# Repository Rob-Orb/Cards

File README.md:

# Cards

## KiCad Configuration

In Eeschema :
You should find the library in the folder [kicad-symbols](kicad-symbols). Link this library to kicad.

- Preferences -> Symbol Library Manager -> Browse Library...

| Nickname | Library Path | Plugin Type |
| ------------- | ------------- | ------------- |
| Rob | ../../Rob-5.lib | Legacy |

In PCBNew :
- Preferences -> Footprint Library Manager -> Append Library

| Nickname | Library Path | Plugin Type |
| ------------- | ------------- | ------------- |
| Rob | https://github.com/Rob-Orb/Rob-5.0.pretty | Github |

Or if you want to modify the library after cloning it :

| Nickname | Library Path | Plugin Type |
| ------------- | ------------- | ------------- |
| Rob | ${KIPRJMOD}/../../../Rob-5.0.pretty | KiCad |

And clone the library [Rob.pretty](https://github.com/Rob-Orb/Rob.pretty) at the corresponding path (next to this repo).

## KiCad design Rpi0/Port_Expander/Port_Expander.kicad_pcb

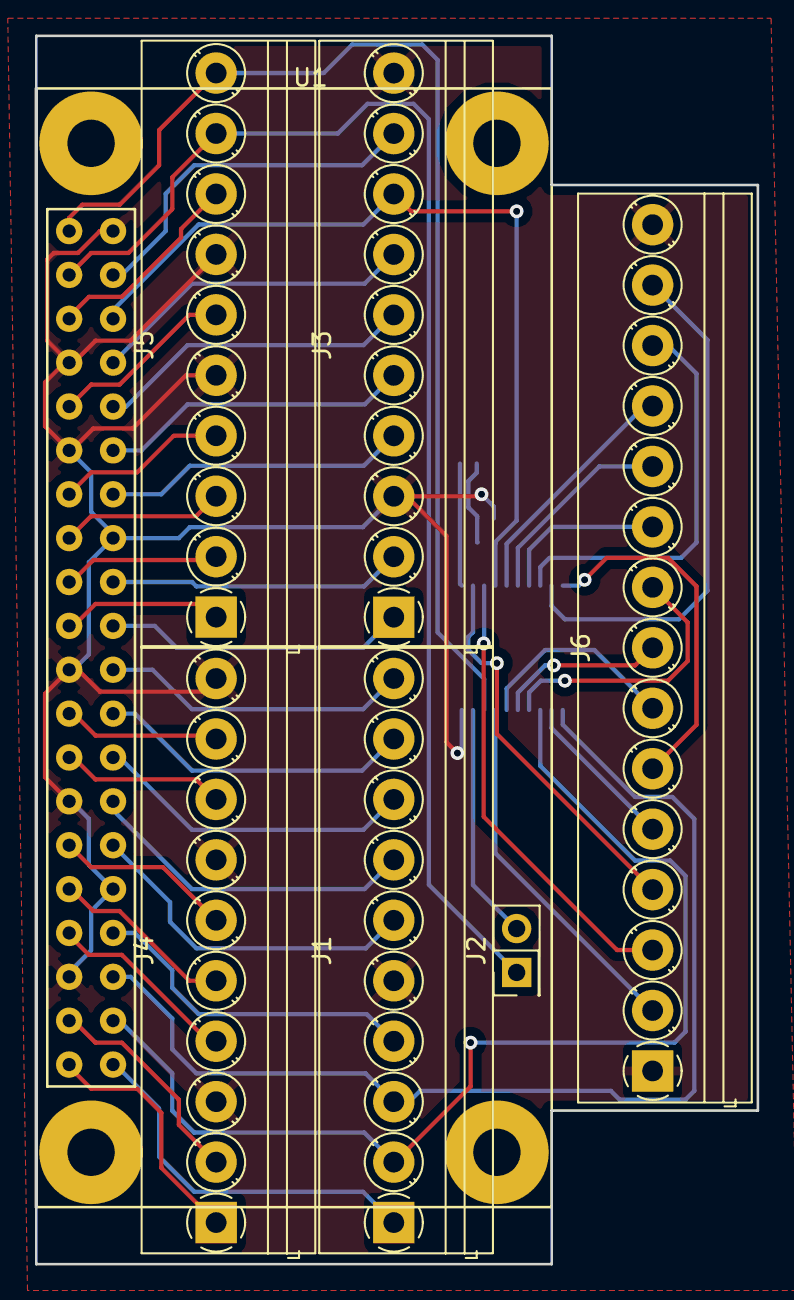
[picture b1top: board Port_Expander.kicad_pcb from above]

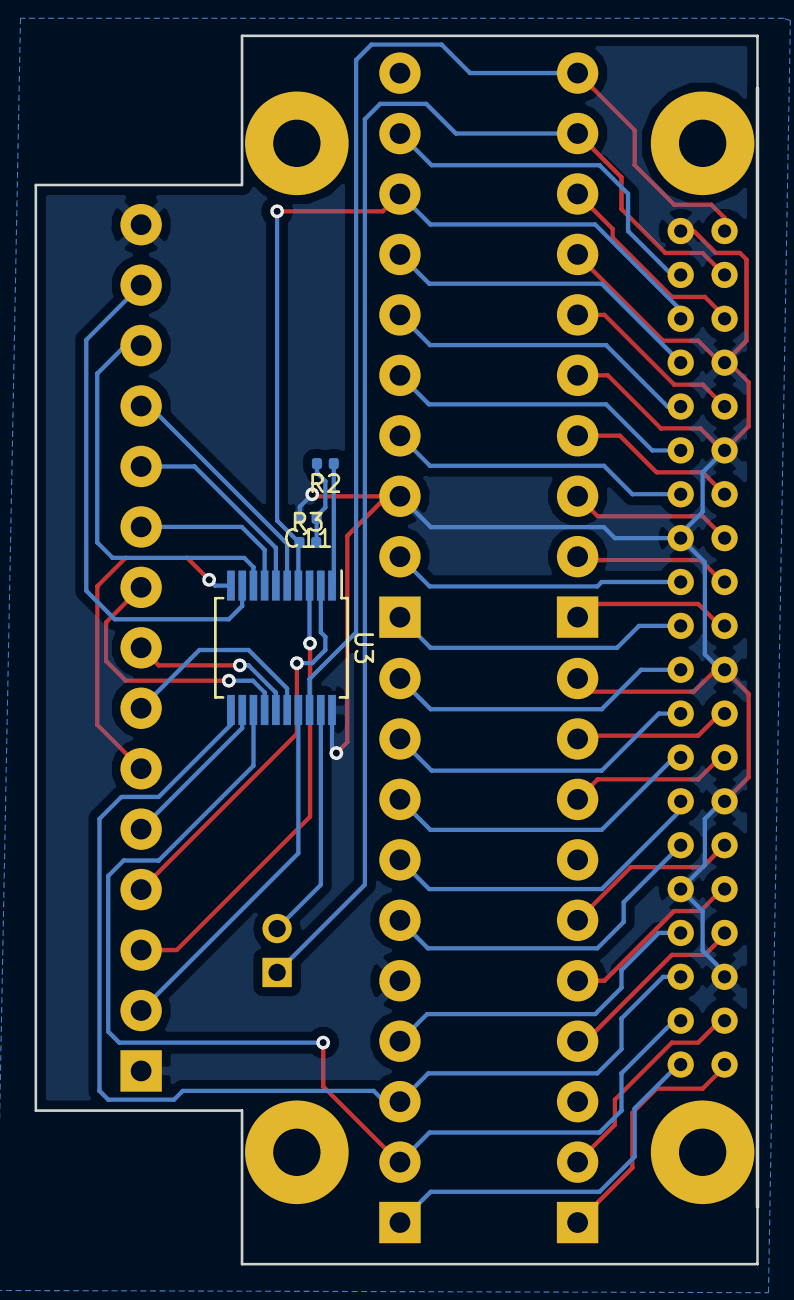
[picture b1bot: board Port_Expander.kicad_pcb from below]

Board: 2 copper layers, 41.8 x 71.1 mm, 11 parts (4 on the bottom side), 49 nets.

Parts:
C11: 1uF; C_0402_1005Metric
J1, J3, J4, J5: Screw_Terminal_01x10; TerminalBlock_Phoenix_MKDS-1,5-10-3.5-H_1x10_P3.50mm_Horizo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
J2: Conn_02x01; PinHeader_2x01_P2.54mm_Vertical
J6: Screw_Terminal_01x15; TerminalBlock_Phoenix_MKDS-1,5-15-3.5-H_1x15_P3.50mm_Horizo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
R2: 10k; R_0402_1005Metric
R3: 470; R_0402_1005Metric
U1: RPI0-Template; RPi0_Template
U3: PIC16F1509-ISS; SSOP-20_5.3x7.2mm_P0.65mm

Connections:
+3V3: R2.1, U3.1
/PIC16LF1509/RA2: J6.2, U3.17
/PIC16LF1509/RA4: J6.3, U3.3
/PIC16LF1509/RA5: J6.4, U3.2
/PIC16LF1509/RB5: J6.5, U3.12
/PIC16LF1509/RB7: J6.6, U3.10
/PIC16LF1509/RC0: J6.7, U3.16
/PIC16LF1509/RC1: J6.8, U3.15
/PIC16LF1509/RC2: J6.9, U3.14
/PIC16LF1509/RC3: J6.10, U3.7
/PIC16LF1509/RC4: J6.11, U3.6
/PIC16LF1509/RC5: J6.12, U3.5
/PIC16LF1509/RC6: J6.13, U3.8
/PIC16LF1509/RC7: J6.14, U3.9
GND: C11.2, J1.5, J3.3, J3.10, J4.3, J4.7, J4.10, J5.5, J5.7, J6.1, J6.15, U1.6, U1.9, U1.14, U1.20, U1.25, U1.30, U1.34, U1.39, U3.20
ISCP_CLK: J5.10, U1.40, U3.18
ISCP_DAT: J2.1, J5.9, U1.38
MCLR: J3.8, R3.1, U1.35, U3.4
unnamed: C11.1, R2.2, R3.2
unnamed: J1.1, U1.1
unnamed: J1.4, U1.7
unnamed: J1.6, U1.11
unnamed: J1.7, U1.13
unnamed: J1.8, U1.15
unnamed: J1.9, U1.17
unnamed: J1.10, U1.19
unnamed: J2.2, U3.19
unnamed: J3.1, U1.21
unnamed: J3.2, U1.23
unnamed: J3.4, U1.27
unnamed: J3.5, U1.29
unnamed: J3.6, U1.31
unnamed: J3.7, U1.33
unnamed: J3.9, U1.37
unnamed: J4.1, U1.2
unnamed: J4.2, U1.4
unnamed: J4.4, U1.8
unnamed: J4.5, U1.10
unnamed: J4.6, U1.12
unnamed: J4.8, U1.16
unnamed: J4.9, U1.18
unnamed: J5.1, U1.22
unnamed: J5.2, U1.24
unnamed: J5.3, U1.26
unnamed: J5.4, U1.28
unnamed: J5.6, U1.32
unnamed: J5.8, U1.36
SCL: J1.3, U1.5, U3.11
SDA: J1.2, U1.3, U3.13

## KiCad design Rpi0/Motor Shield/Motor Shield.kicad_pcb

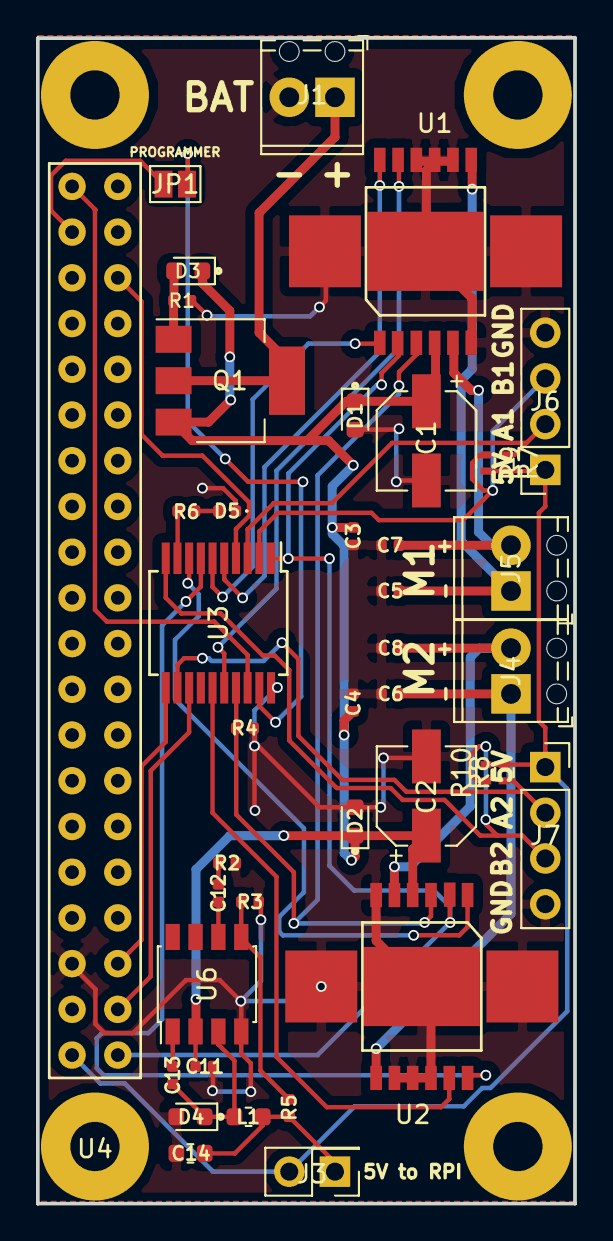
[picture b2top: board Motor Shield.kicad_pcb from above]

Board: 2 copper layers, 29.8 x 64.8 mm, 41 parts (0 on the bottom side), 35 nets.

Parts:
C1, C2: 100uF; CP_Elec_5x5.3
C3, C4: 100nF; C_0402_1005Metric
C5, C6, C7, C8, C13: 10nF; C_0402_1005Metric
C11: 10uF; C_0402_1005Metric
C12: 2.2nF; C_0402_1005Metric
C14: 22uF; C_0603_1608Metric
D1, D2: < 40V; D_0603_1608Metric
D3: 10V; D_0603_1608Metric
D4: 40V; D_0603_1608Metric
D5: GREEN; LED_0402_1005Metric
J1, J4, J5: Screw_Terminal_01x02; TerminalBlock_Phoenix_MPT-0,5-2-2.54_1x02_P2.54mm_Horizontal
J3: Conn_02x01; PinHeader_2x01_P2.54mm_Vertical
J6, J7: Conn_01x04_Female; PinSocket_1x04_P2.54mm_Vertical
JP1: SolderJumper_2_Open; SolderJumper-2_P1.3mm_Open_Pad1.0x1.5mm
L1: 15uH; L_0603_1608Metric
Q1: Q_PMOS_GDSD; SOT-223
R1, R3, R4: 10k; R_0402_1005Metric
R2: 15k; R_0402_1005Metric
R5: 28.7k; R_0402_1005Metric
R6: 50; R_0402_1005Metric
R7, R8, R9, R10: 1k; R_0402
U1, U2: IFX9201SG
U3: PIC16F1509-ISS; SSOP-20_5.3x7.2mm_P0.65mm
U4: RPI0-Template; RPi0_Template
U6: ACT4060A; SSOP-8_3.95x5.21x3.27mm_P1.27mm

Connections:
5V: C14.1, J3.1, L1.2, R5.1
+3V3: U1.2, U2.2, U3.1, U4.1
+5V: J3.2, J6.1, J7.1, R7.2, R8.2, R9.2, R10.2, U4.2
/PIC16LF1509/Bonus: R6.1, U3.9
A1: J6.2, R7.1, U3.3
A2: J7.2, R8.1, U3.12
B1: J6.3, R9.1, U3.2
B2: J7.3, R10.1, U3.10
BAT+: J1.1, Q1.2, Q1.4
BAT-: C1.2, C2.2, C3.2, C4.2, C5.2, C6.2, C7.2, C8.2, C11.2, C14.2, D1.2, D2.2, D4.2, D5.1, J1.2, J6.4, J7.4, R1.2, R2.2, R3.2, R4.2, U1.6, U1.8, U1.9, U1.10, U1.~, U2.6, U2.8, U2.9, U2.10, U2.~, U3.20, U4.6, U6.4
BAT-PROT+: C1.1, C2.1, C3.1, C4.1, C11.1, D1.1, D2.1, D3.1, Q1.3, U1.4, U2.4, U6.2
DIR1: U1.1, U3.6
DIR2: U2.1, U3.8
EN1: U1.11, U3.16
EN2: U2.11, U3.15
ERROR: R4.1, U1.3, U2.3, U3.17
ICSP_CLK: U3.18, U4.40
ICSP_DAT: JP1.1, U4.38
MCLR: U3.4, U4.35
unnamed: C12.1, U6.6
unnamed: C12.2, R2.1
unnamed: C13.1, U6.1
unnamed: C13.2, D4.1, L1.1, U6.3
unnamed: D3.2, Q1.1, R1.1
unnamed: D5.2, R6.2
unnamed: JP1.2, U3.19
unnamed: R3.1, R5.2, U6.5
OUT1: C7.1, J5.2, U1.5
OUT2: C5.1, J5.1, U1.7
OUT3: C8.1, J4.2, U2.5
OUT4: C6.1, J4.1, U2.7
PWM1: U1.12, U3.5
PWM2: U2.12, U3.7
SCL: U3.11, U4.5
SDA: U3.13, U4.3

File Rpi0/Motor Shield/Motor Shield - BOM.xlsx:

Reference | Value | Footprint | Datasheet
R3 | 470 | Resistor_SMD:R_0402_1005Metric
D1 | < 40V | Diode_SMD:D_0603_1608Metric
D2 | < 40V | Diode_SMD:D_0603_1608Metric
C3 | 100nF | Capacitor_SMD:C_0402_1005Metric
C4 | 100nF | Capacitor_SMD:C_0402_1005Metric
C9 | 100nF | Capacitor_SMD:C_0402_1005Metric
C1 | 100uF | Capacitor_SMD:CP_Elec_5x5.3
C2 | 100uF | Capacitor_SMD:CP_Elec_5x5.3
R1 | 10k | Resistor_SMD:R_0402_1005Metric
R2 | 10k | Resistor_SMD:R_0402_1005Metric
C5 | 10nF | Capacitor_SMD:C_0603_1608Metric
C7 | 10nF | Capacitor_SMD:C_0603_1608Metric
C6 | 10nF | Capacitor_SMD:C_0603_1608Metric
C8 | 10nF | Capacitor_SMD:C_0603_1608Metric
C10 | 10uF | Capacitor_SMD:C_0603_1608Metric
D3 | 10V | Diode_SMD:D_0603_1608Metric
C11 | 1uF | Capacitor_SMD:C_0402_1005Metric
J6 | Conn_01x04_Female | Connector_PinSocket_2.54mm:PinSocket_1x04_P2.54mm_Vertical | ~
J7 | Conn_01x04_Female | Connector_PinSocket_2.54mm:PinSocket_1x04_P2.54mm_Vertical | ~
J3 | Conn_02x01 | Connector_PinHeader_2.54mm:PinHeader_2x01_P2.54mm_Vertical | ~
J2 | Conn_02x01 | Connector_PinHeader_2.54mm:PinHeader_2x01_P2.54mm_Vertical | ~
U1 | IFX9201SG | Rob-5.0:IFX9201SG
U2 | IFX9201SG | Rob-5.0:IFX9201SG
U5 | LD1117S50TR_SOT223 | Package_TO_SOT_SMD:SOT-223-3_TabPin2 | http://www.st.com/st-web-ui/static/active/en/resource/techni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
U3 | PIC16F1509-ISS | Package_SO:SSOP-20_5.3x7.2mm_P0.65mm | http://ww1.microchip.com/downloads/en/DeviceDoc/41609A.pdf
Q1 | Q_PMOS_GDSD | Package_TO_SOT_SMD:SOT-223
U4 | RPI0-Template | Rob-5.0:RPi0_Template
J1 | Screw_Terminal_01x02 | TerminalBlock_Phoenix:TerminalBlock_Phoenix_MPT-0,5-2-2.54_1x02_P2.54mm_Horizon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 | ~
J5 | Screw_Terminal_01x02 | TerminalBlock_Phoenix:TerminalBlock_Phoenix_MPT-0,5-2-2.54_1x02_P2.54mm_Horizon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 | ~
J4 | Screw_Terminal_01x02 | TerminalBlock_Phoenix:TerminalBlock_Phoenix_MPT-0,5-2-2.54_1x02_P2.54mm_Horizon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 | ~

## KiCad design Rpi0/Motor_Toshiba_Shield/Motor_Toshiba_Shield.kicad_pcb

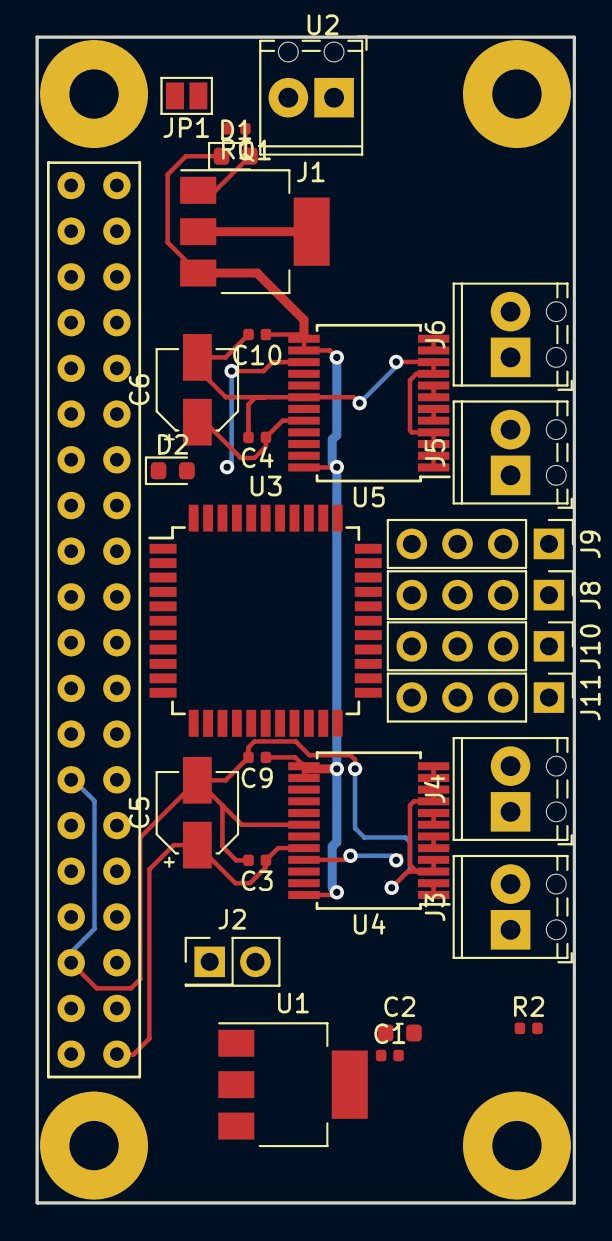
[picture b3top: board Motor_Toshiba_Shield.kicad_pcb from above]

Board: 2 copper layers, 29.8 x 64.8 mm, 29 parts (0 on the bottom side), 45 nets.

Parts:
C1, C3, C4, C9, C10: 100nF; C_0402_1005Metric
C2: 10uF; C_0603_1608Metric
C5, C6: 10uF; CP_Elec_4x5.4
D1: D_Schottky; D_0603_1608Metric
D2: LED; LED_0603_1608Metric
J1, J3, J4, J5, J6: Screw_Terminal_01x02; TerminalBlock_Phoenix_MPT-0,5-2-2.54_1x02_P2.54mm_Horizontal
J2: Conn_02x01; PinHeader_2x01_P2.54mm_Vertical
J8, J9, J10, J11: Conn_01x04_Female; PinHeader_1x04_P2.54mm_Vertical
JP1: SolderJumper_2_Open; SolderJumper-2_P1.3mm_Open_Pad1.0x1.5mm
Q1: Q_NMOS_GDSD; SOT-223
R1: 10k; R_0402_1005Metric
R2: 50; R_0402_1005Metric
U1: LD1117S50TR_SOT223; SOT-223-3_TabPin2
U2: RPI0-Template; RPi0_Template
U3: PIC16F1777-TQFP; TQFP-44_10x10mm_P0.8mm
U4, U5: TB6612FNG; SSOP-24_5.3x8.2mm_P0.65mm

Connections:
+3V3: C3.1, C4.1, C5.1, C6.1, U2.1, U3.7, U3.28, U4.20, U5.20
+5V: C2.1, J2.1, J8.1, J9.1, J10.1, J11.1, U1.2
A1: J8.2, U3.23
A2: J9.2, U3.31
A3: J10.2, U3.8
A4: J11.2, U3.10
B1: J8.3, U3.24
B2: J9.3, U3.30
B3: J10.3, U3.9
B4: J11.3, U3.11
BAT+: J1.1, Q1.2, Q1.4
BAT-: C1.2, C2.2, C3.2, C4.2, C5.2, C6.2, C9.2, C10.2, D2.1, J1.2, J8.4, J9.4, J10.4, J11.4, R1.2, U1.1, U2.6, U2.14, U2.39, U3.6, U3.29, U4.3, U4.4, U4.9, U4.10, U4.18, U5.3, U5.4, U5.9, U5.10, U5.18
BAT-PROT+: C1.1, C9.1, C10.1, D1.1, Q1.3, U1.3, U4.13, U4.14, U4.24, U5.13, U5.14, U5.24
EN1: U3.25, U5.19
EN2: U3.26, U4.19
ICSP_CLK: U2.40, U3.16
ICSP_DAT: JP1.2, U2.38
INA1: U3.38, U5.21
INA2: U3.39, U5.22
INA3: U3.2, U4.21
INA4: U3.3, U4.22
INB1: U3.40, U5.17
INB2: U3.41, U5.16
INB3: U3.4, U4.17
INB4: U3.5, U4.16
MCLR: U2.35, U3.18
unnamed: D1.2, Q1.1, R1.1
unnamed: D2.2, R2.2
unnamed: J2.2, U2.2
unnamed: J3.1, U4.1, U4.2
unnamed: J3.2, U4.5, U4.6
unnamed: J4.1, U4.7, U4.8
unnamed: J4.2, U4.11, U4.12
unnamed: J5.1, U5.1, U5.2
unnamed: J5.2, U5.5, U5.6
unnamed: J6.1, U5.7, U5.8
unnamed: J6.2, U5.11, U5.12
unnamed: JP1.1, U3.17
unnamed: R2.1, U3.14
PWM1: U3.20, U5.23
PWM2: U3.21, U5.15
PWM3: U3.22, U4.23
PWM4: U3.19, U4.15
SCL: U2.5, U3.37
SDA: U2.3, U3.42

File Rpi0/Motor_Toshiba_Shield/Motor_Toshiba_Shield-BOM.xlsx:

Reference | Value | Footprint | Datasheet
R3 | 470 | Resistor_SMD:R_0402_1005Metric
C3 | 100nF | Capacitor_SMD:C_0402_1005Metric | ~
C4 | 100nF | Capacitor_SMD:C_0402_1005Metric | ~
C10 | 100nF | Capacitor_SMD:C_0402_1005Metric | ~
C9 | 100nF | Capacitor_SMD:C_0402_1005Metric | ~
C1 | 100nF | Capacitor_SMD:C_0402_1005Metric | ~
R1 | 10k | Resistor_SMD:R_0402_1005Metric | ~
R2 | 10k | Resistor_SMD:R_0402_1005Metric
C5 | 10uF | Capacitor_SMD:CP_Elec_4x5.4 | ~
C6 | 10uF | Capacitor_SMD:CP_Elec_4x5.4 | ~
C2 | 10uF | Capacitor_SMD:C_0603_1608Metric | ~
C11 | 1uF | Capacitor_SMD:C_0402_1005Metric
J8 | Conn_01x04_Female | Connector_PinHeader_2.54mm:PinHeader_1x04_P2.54mm_Vertical | ~
J9 | Conn_01x04_Female | Connector_PinHeader_2.54mm:PinHeader_1x04_P2.54mm_Vertical | ~
J10 | Conn_01x04_Female | Connector_PinHeader_2.54mm:PinHeader_1x04_P2.54mm_Vertical | ~
J11 | Conn_01x04_Female | Connector_PinHeader_2.54mm:PinHeader_1x04_P2.54mm_Vertical | ~
J2 | Conn_02x01 | Connector_PinHeader_2.54mm:PinHeader_2x01_P2.54mm_Vertical | ~
J7 | Conn_02x01 | Connector_PinHeader_2.54mm:PinHeader_2x01_P2.54mm_Vertical | ~
D1 | D_Schottky | Diode_SMD:D_0603_1608Metric | ~
U1 | LD1117S50TR_SOT223 | Package_TO_SOT_SMD:SOT-223-3_TabPin2 | http://www.st.com/st-web-ui/static/active/en/resource/techni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
U3 | MCP23008_SSOP | Package_SO:SSOP-20_5.3x7.2mm_P0.65mm | http://ww1.microchip.com/downloads/en/DeviceDoc/21919e.pdf
U6 | PIC16F1509-ISS | Package_SO:SSOP-20_5.3x7.2mm_P0.65mm | http://ww1.microchip.com/downloads/en/DeviceDoc/41609A.pdf
Q1 | Q_NMOS_GDSD | Package_TO_SOT_SMD:SOT-223 | ~
U2 | RPI0-Template | Rob-5.0:RPi0_Template
J1 | Screw_Terminal_01x02 | TerminalBlock_Phoenix:TerminalBlock_Phoenix_MPT-0,5-2-2.54_1x02_P2.54mm_Horizon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 | ~
J5 | Screw_Terminal_01x02 | TerminalBlock_Phoenix:TerminalBlock_Phoenix_MPT-0,5-2-2.54_1x02_P2.54mm_Horizon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 | ~
J6 | Screw_Terminal_01x02 | TerminalBlock_Phoenix:TerminalBlock_Phoenix_MPT-0,5-2-2.54_1x02_P2.54mm_Horizon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 | ~
J3 | Screw_Terminal_01x02 | TerminalBlock_Phoenix:TerminalBlock_Phoenix_MPT-0,5-2-2.54_1x02_P2.54mm_Horizon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 | ~
J4 | Screw_Terminal_01x02 | TerminalBlock_Phoenix:TerminalBlock_Phoenix_MPT-0,5-2-2.54_1x02_P2.54mm_Horizon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 | ~
JP1 | SolderJumper_2_Open | Jumper:SolderJumper-2_P1.3mm_Open_Pad1.0x1.5mm | ~
JP2 | SolderJumper_2_Open | Jumper:SolderJumper-2_P1.3mm_Open_Pad1.0x1.5mm | ~
JP3 | SolderJumper_2_Open | Jumper:SolderJumper-2_P1.3mm_Open_Pad1.0x1.5mm | ~
U5 | TB6612FNG | Package_SO:SSOP-24_5.3x8.2mm_P0.65mm | https://toshiba.semicon-storage.com/us/product/linear/motord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
U4 | TB6612FNG | Package_SO:SSOP-24_5.3x8.2mm_P0.65mm | https://toshiba.semicon-storage.com/us/product/linear/motord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

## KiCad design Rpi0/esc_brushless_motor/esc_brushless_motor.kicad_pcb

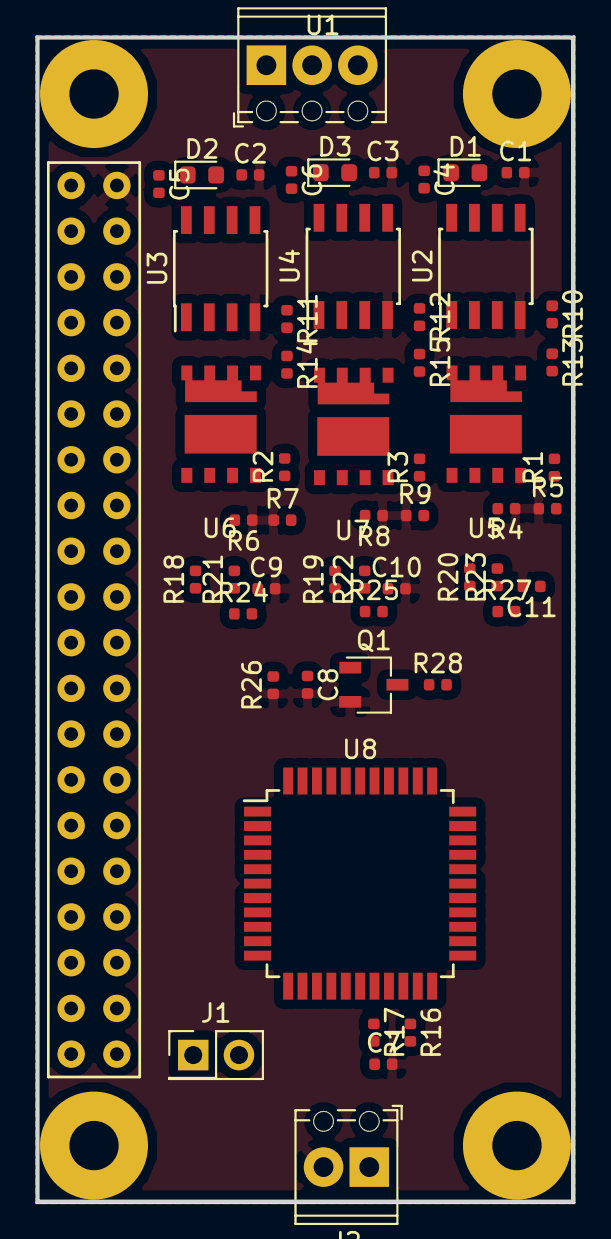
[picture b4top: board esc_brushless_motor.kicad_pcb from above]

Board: 2 copper layers, 29.7 x 64.6 mm, 54 parts (0 on the bottom side), 42 nets, no tracks yet.

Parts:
C1, C2, C3, C4, C5, C6: 1u_10V; C_0402_1005Metric
C7: 1uF; C_0402_1005Metric
C8: 100n; C_0402_1005Metric
C9, C10, C11: 47p; C_0402_1005Metric
D1, D2, D3: BAT54-02V; D_0603_1608Metric
J1: Conn_02x01; PinHeader_2x01_P2.54mm_Vertical
J2: Screw_Terminal_01x02; TerminalBlock_Phoenix_MPT-0,5-2-2.54_1x02_P2.54mm_Horizontal
J3: Screw_Terminal_01x03; TerminalBlock_Phoenix_MPT-0,5-3-2.54_1x03_P2.54mm_Horizontal
Q1: Q_NPN_BEC; TSOT-23
R1, R2, R3, R13, R14, R15: 100; R_0402_1005Metric
R4, R6, R8: Shunt; R_0402_1005Metric
R5, R7, R9, R10, R11, R12, R16, R24, R25, R26, R27: 10k; R_0402_1005Metric
R17: 470; R_0402_1005Metric
R18, R19, R20, R21, R22, R23: 1k; R_0402_1005Metric
R28: 3.3k; R_0402_1005Metric
U1: RPI0-Template; RPi0_Template
U2, U3, U4: IR2301; SOIC-8_3.9x4.9mm_P1.27mm
U5, U6, U7: BSC0925ND
U8: PIC16F1777-TQFP; TQFP-44_10x10mm_P0.8mm

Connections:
+3V3: R16.1, R24.2, R25.2, R27.2, R28.2, U1.1, U8.7, U8.28
GND: C1.2, C2.2, C3.2, C7.2, C8.2, C9.2, C10.2, C11.2, J2.2, Q1.2, R4.1, R5.1, R6.1, R7.1, R8.1, R9.1, R26.1, U1.39, U2.4, U3.4, U4.4, U8.6, U8.29
HO1: R14.1, U3.7
HO2: R15.1, U4.7
HO3: R13.1, U2.7
H_U: U3.2, U8.2
H_V: U4.2, U8.38
H_W: U2.2, U8.40
ICSP_CLK: U1.40, U8.16
ICSP_DAT: J1.1, U1.38
LO1: R2.2, U3.5
LO2: R3.2, U4.5
LO3: R1.2, U2.5
L_U: U3.3, U8.3
L_V: U4.3, U8.39
L_W: U2.3, U8.41
MCLR: R17.1, U1.35, U8.18
unnamed: C4.1, D1.1, U2.8
unnamed: C5.1, D2.1, U3.8
unnamed: C6.1, D3.1, U4.8
unnamed: C7.1, R16.2, R17.2
unnamed: C8.1, Q1.1, R18.1, R19.1, R20.1, R26.2
unnamed: J1.2, U8.17
unnamed: R1.1, R5.2, U5.8
unnamed: R2.1, R7.2, U6.8
unnamed: R3.1, R9.2, U7.8
unnamed: R10.2, R13.2, U5.1
unnamed: R11.2, R14.2, U6.1
unnamed: R12.2, R15.2, U7.1
SCL: U1.5, U8.37
SDA: U1.3, U8.42
SENSE_U: C9.1, R21.1, R24.1, U8.19
SENSE_V: C10.1, R22.1, R25.1, U8.20
SENSE_W: C11.1, R23.1, R27.1, U8.21
S_U: R6.2, R18.2, R21.2, U6.5, U6.6, U6.7
S_V: R8.2, R19.2, R22.2, U7.5, U7.6, U7.7
S_W: R4.2, R20.2, R23.2, U5.5, U5.6, U5.7
U: C5.2, J3.1, R11.1, U3.6, U6.9
V: C6.2, J3.2, R12.1, U4.6, U7.9
VCC: C1.1, C2.1, C3.1, D1.2, D2.2, D3.2, J2.1, U2.1, U3.1, U4.1, U5.2, U5.3, U5.4, U6.2, U6.3, U6.4, U7.2, U7.3, U7.4
W: C4.2, J3.3, R10.1, U2.6, U5.9
trap: Q1.3, R28.1, U8.32

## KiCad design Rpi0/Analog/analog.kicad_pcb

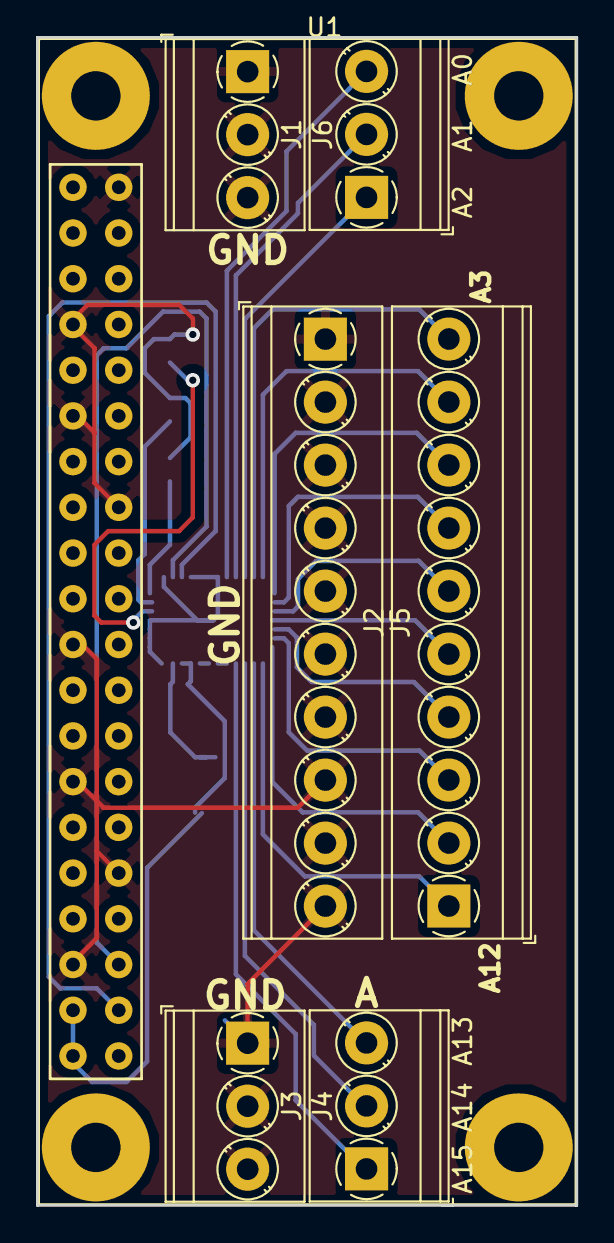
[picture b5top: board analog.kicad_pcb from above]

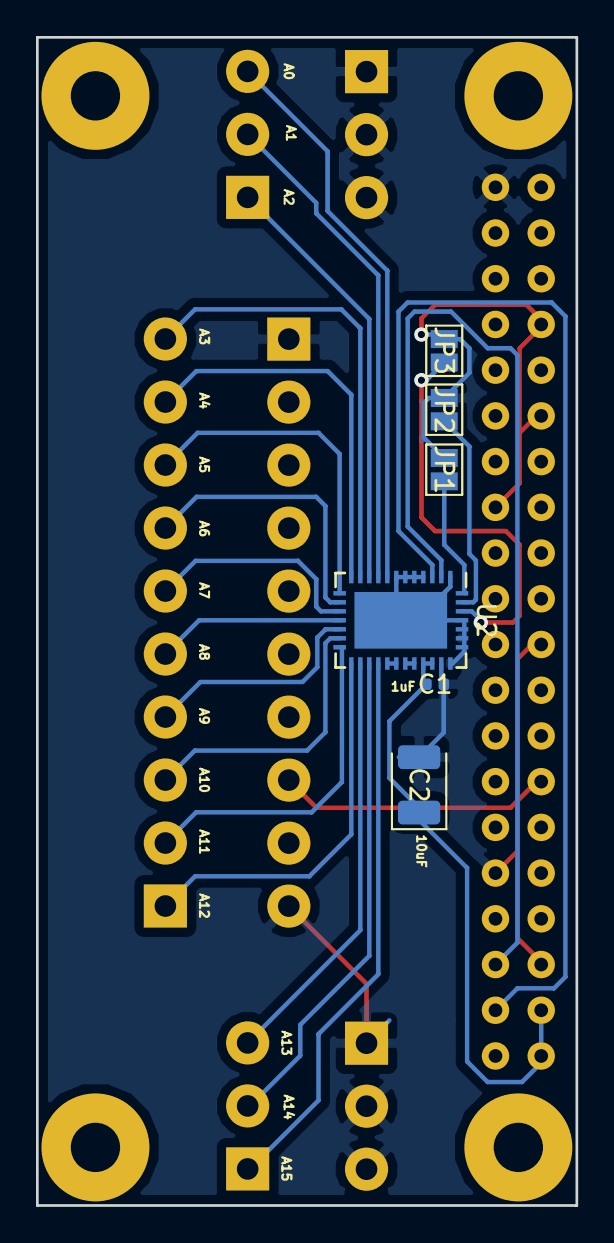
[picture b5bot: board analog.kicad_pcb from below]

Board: 2 copper layers, 30.0 x 64.9 mm, 13 parts (6 on the bottom side), 25 nets.

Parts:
C1: 0.1uF; C_0402_1005Metric
C2: 10uF; CP_EIA-3528-21_Kemet-B
J1, J3, J4, J6: Screw_Terminal_01x03; TerminalBlock_Phoenix_PT-1,5-3-3.5-H_1x03_P3.50mm_Horizontal
J2, J5: Screw_Terminal_01x10; TerminalBlock_Phoenix_PT-1,5-10-3.5-H_1x10_P3.50mm_Horizont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
JP1, JP2, JP3: SolderJumper_2_Open; SolderJumper-2_P1.3mm_Open_Pad1.0x1.5mm
U1: RPI0-Template; RPi0_Template
U2: LTC2495; QFN-38-1EP_5x7mm_P0.5mm_EP3.15x5.15mm

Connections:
5V: C1.1, C2.1, U1.2, U1.4, U2.28, U2.29
GND: C1.2, C2.2, J4.1, J4.2, J4.3, J5.1, J5.2, J5.3, J5.4, J5.5, J5.6, J5.7, J5.8, J5.9, J5.10, J6.1, J6.2, J6.3, JP1.1, JP2.1, JP3.1, U1.6, U1.9, U1.14, U1.20, U1.25, U1.30, U1.34, U1.39, U2.1, U2.4, U2.5, U2.6, U2.7, U2.30, U2.31, U2.32, U2.33, U2.34, U2.35, U2.39
unnamed: J1.1, U2.10
unnamed: J1.2, U2.9
unnamed: J1.3, U2.8
unnamed: J2.1, U2.20
unnamed: J2.2, U2.19
unnamed: J2.3, U2.18
unnamed: J2.4, U2.17
unnamed: J2.5, U2.16
unnamed: J2.6, U2.15
unnamed: J2.7, U2.14
unnamed: J2.8, U2.13
unnamed: J2.9, U2.12
unnamed: J2.10, U2.11
unnamed: J3.1, U2.23
unnamed: J3.2, U2.22
unnamed: J3.3, U2.21
unnamed: JP1.2, U2.38
unnamed: JP2.2, U2.37
unnamed: JP3.2, U2.36
unnamed: U2.24, U2.25
unnamed: U2.26, U2.27
SCL: U1.5, U2.2
SDA: U1.3, U2.3

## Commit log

2018-09-17 Motor Shield Begin
2018-09-17 [KICAD]Changed directory for kicad libraries to fetch online
2018-09-17 [KICAD]Standard library folder hierarchy
2018-09-17 [Shit] New repo needed for kicad github imports
2018-09-17 [KICAD]Changed path to relative to libraries
2018-09-17 [RPI0] [Motor Shield] Almost finished version, need to trace
2018-09-18 Almost finished circuit for motor shield
2018-09-18 Motor shield traced and finished
2018-09-18 Add instructions for KiCad
2018-09-19 Changed TL5569 to PIC16F1509
2018-10-02 Added ICSP to microchip pic
2018-10-05 Removed unnecessary 3.3V regulator. Added encoder pins with 5v regulator
2018-10-05 Added pins option to power the raspberry pi from the battery
2018-10-05 Added BOM (Bill of Material)
2018-10-08 Upgrade to Kicad 5.0
2018-10-12 Modified components compared to Mouser electronics stocks
2018-10-12 Missing connections
2018-10-15 Updated IFX9201 footprint for thermal pads
2018-10-15 Updated gerber files
2018-10-16 Added template for pic
2018-10-16 Working motor board with TB6612
2018-10-16 Added BOM
2018-10-17 Fixed rpi0 connector
2018-10-17 Fixed rpi0 3d template and rendered final image
2018-10-25 Added Port Expander board
2018-11-05 Update Motor shield BOM
2018-11-05 Added 16-bit analog board
2018-11-05 Cleanup
2018-11-12 Begin joystick board
2018-11-12 Start esc board
2018-11-13 Finished schematics and placement of components
2018-11-19 Updated Regulator, Added text, Changed all pins to pic, better 3d view, REV.1 of board
2018-11-19 Changed footprint
2018-11-19 Motor shield gerber zipped
2018-12-09 Added pull-downs to encoders. Rerouted 5V from encoder to real +5V
2018-12-12 Replaced pic16lf1509 and MCP by pic16f1777
2018-12-13 Fix resistance name. Compiled seed studio compatible BOM
2018-12-14 Changed pull down to pull up on the encoders. Recompiled gerbers
2021-03-12 Added rescue
